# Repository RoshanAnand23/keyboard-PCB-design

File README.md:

# keyboard-PCB-design
learning to design a keyboard from pcb level

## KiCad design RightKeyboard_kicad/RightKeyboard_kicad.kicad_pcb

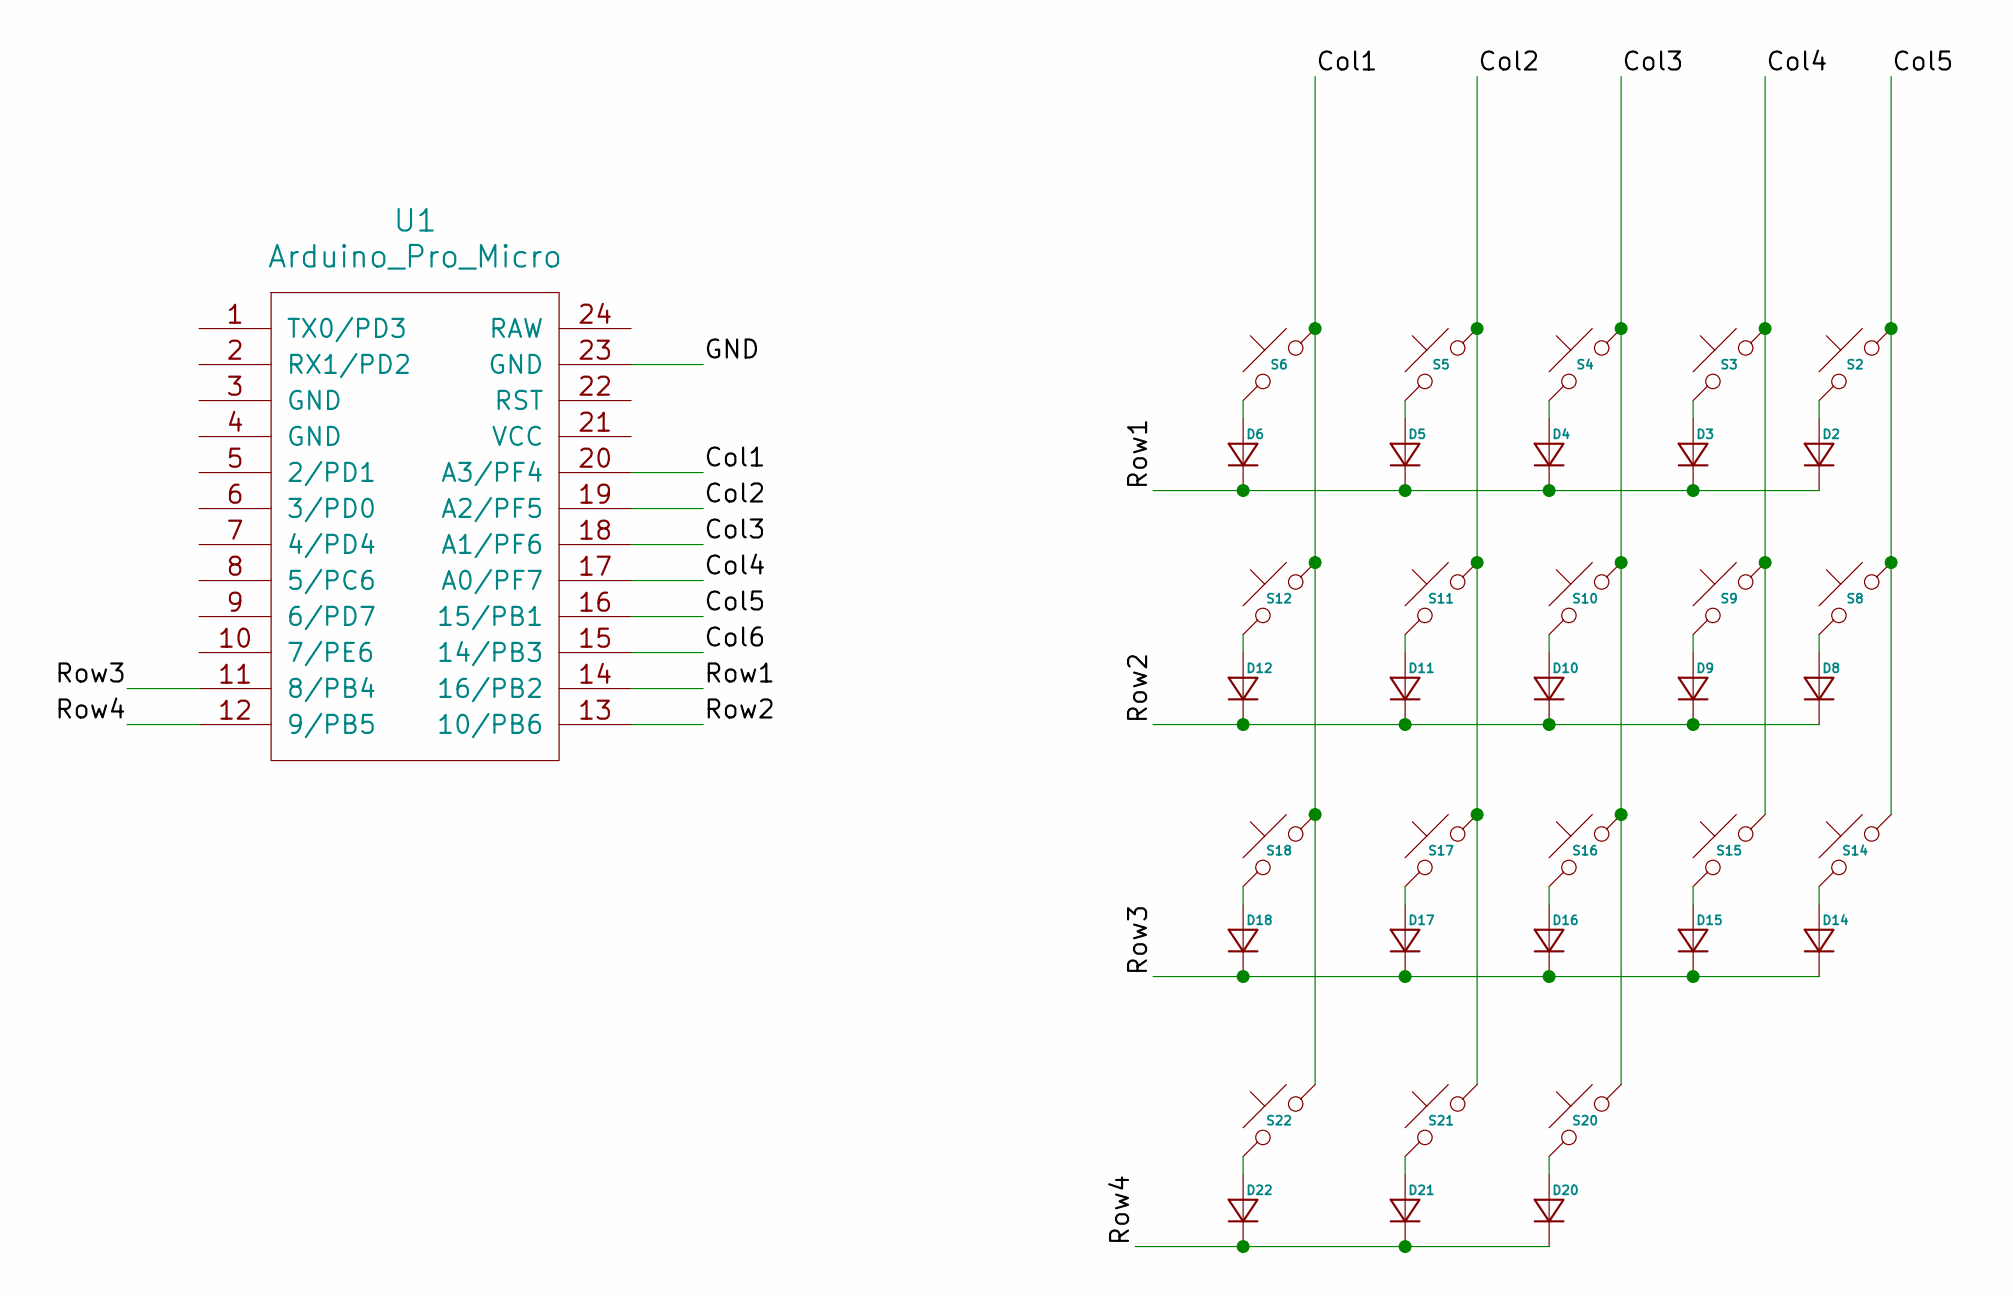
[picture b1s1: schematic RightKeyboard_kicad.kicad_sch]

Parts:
D2, D3, D4, D5, D6, D8, D9, D10, D11, D12, D14, D15, D16, D17, D18, D20, D21, D22: Diode_SOD-123
S2, S3, S4, S5, S6, S8, S9, S10, S11, S12, S14, S15, S16, S17, S18, S20, S21: MX_PCB_1.00u
S22: MX_PCB_1.50u
U1: Arduino_Pro_Micro

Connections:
/Col1: S6.1, S12.1, S18.1, S22.1, U1.20 (A3/PF4)
/Col2: S5.1, S11.1, S17.1, S21.1, U1.19 (A2/PF5)
/Col3: S4.1, S10.1, S16.1, S20.1, U1.18 (A1/PF6)
/Col4: S3.1, S9.1, S15.1, U1.17 (A0/PF7)
/Col5: S2.1, S8.1, S14.1, U1.16 (15/PB1)
/Col6: U1.15 (14/PB3)
/GND: U1.23 (GND)
/Row1: D2.1 (K), D3.1 (K), D4.1 (K), D5.1 (K), D6.1 (K), U1.14 (16/PB2)
/Row2: D8.1 (K), D9.1 (K), D10.1 (K), D11.1 (K), D12.1 (K), U1.13 (10/PB6)
/Row3: D14.1 (K), D15.1 (K), D16.1 (K), D17.1 (K), D18.1 (K), U1.11 (8/PB4)
/Row4: D20.1 (K), D21.1 (K), D22.1 (K), U1.12 (9/PB5)
unnamed: D2.2 (A), S2.2
unnamed: D3.2 (A), S3.2
unnamed: D4.2 (A), S4.2
unnamed: D5.2 (A), S5.2
unnamed: D6.2 (A), S6.2
unnamed: D8.2 (A), S8.2
unnamed: D9.2 (A), S9.2
unnamed: D10.2 (A), S10.2
unnamed: D11.2 (A), S11.2
unnamed: D12.2 (A), S12.2
unnamed: D14.2 (A), S14.2
unnamed: D15.2 (A), S15.2
unnamed: D16.2 (A), S16.2
unnamed: D17.2 (A), S17.2
unnamed: D18.2 (A), S18.2
unnamed: D20.2 (A), S20.2
unnamed: D21.2 (A), S21.2
unnamed: D22.2 (A), S22.2

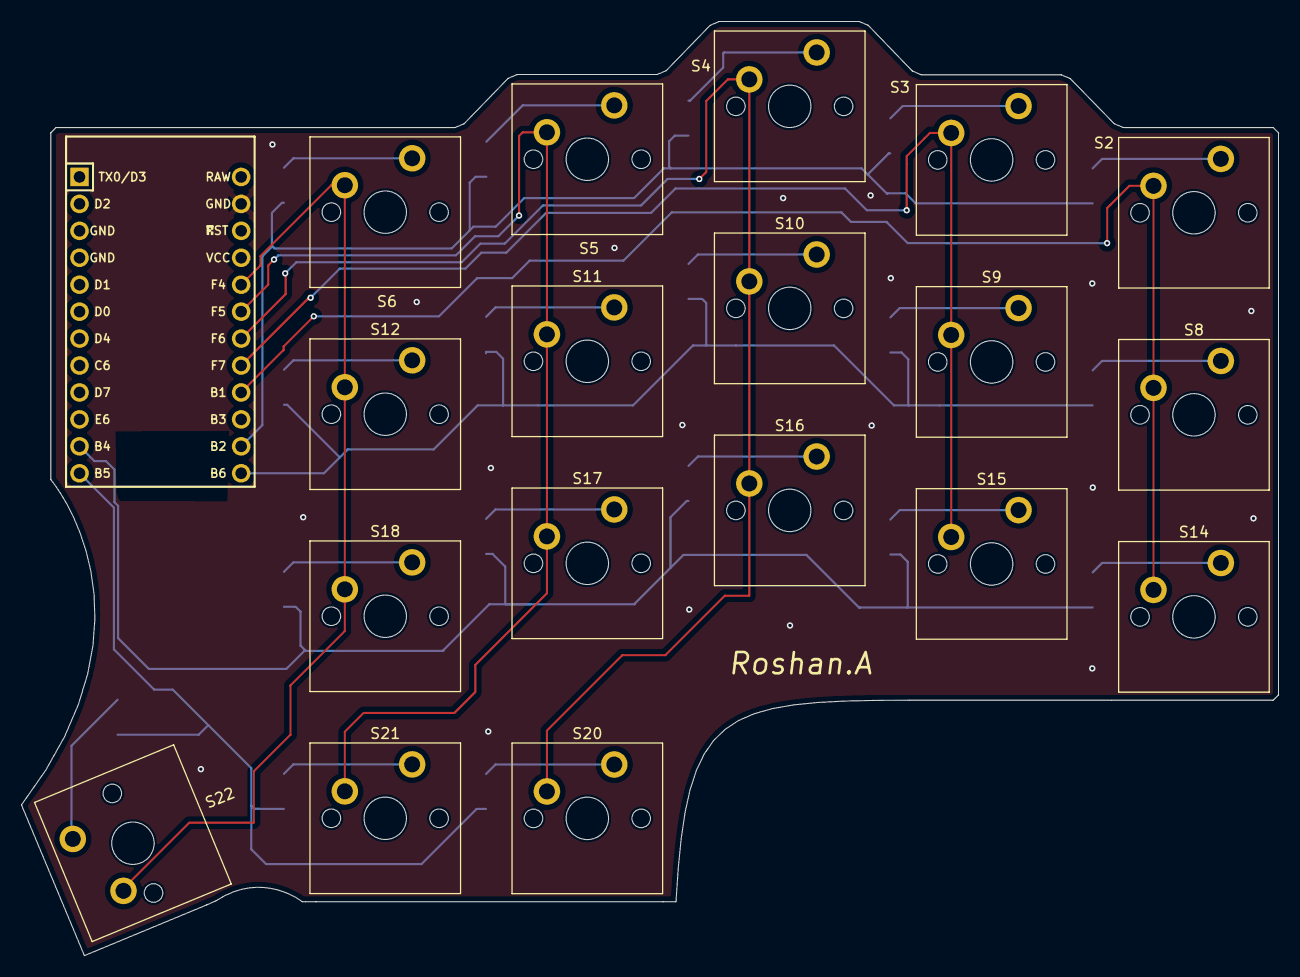
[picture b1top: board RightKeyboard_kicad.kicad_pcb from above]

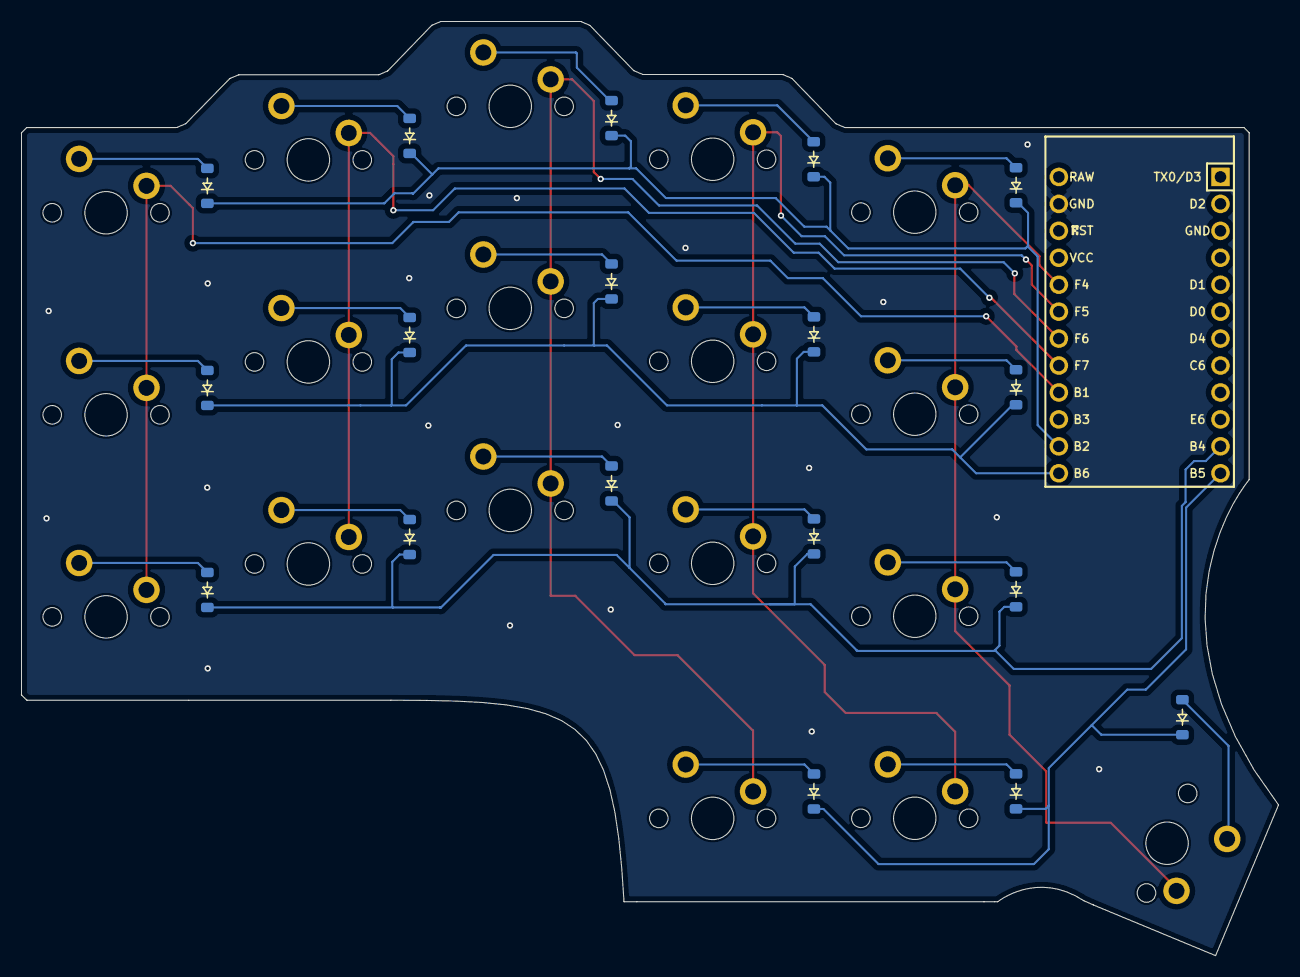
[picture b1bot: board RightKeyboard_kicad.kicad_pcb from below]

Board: 2 copper layers, 118.5 x 88.1 mm, 37 parts (18 on the bottom side), 27 nets.
